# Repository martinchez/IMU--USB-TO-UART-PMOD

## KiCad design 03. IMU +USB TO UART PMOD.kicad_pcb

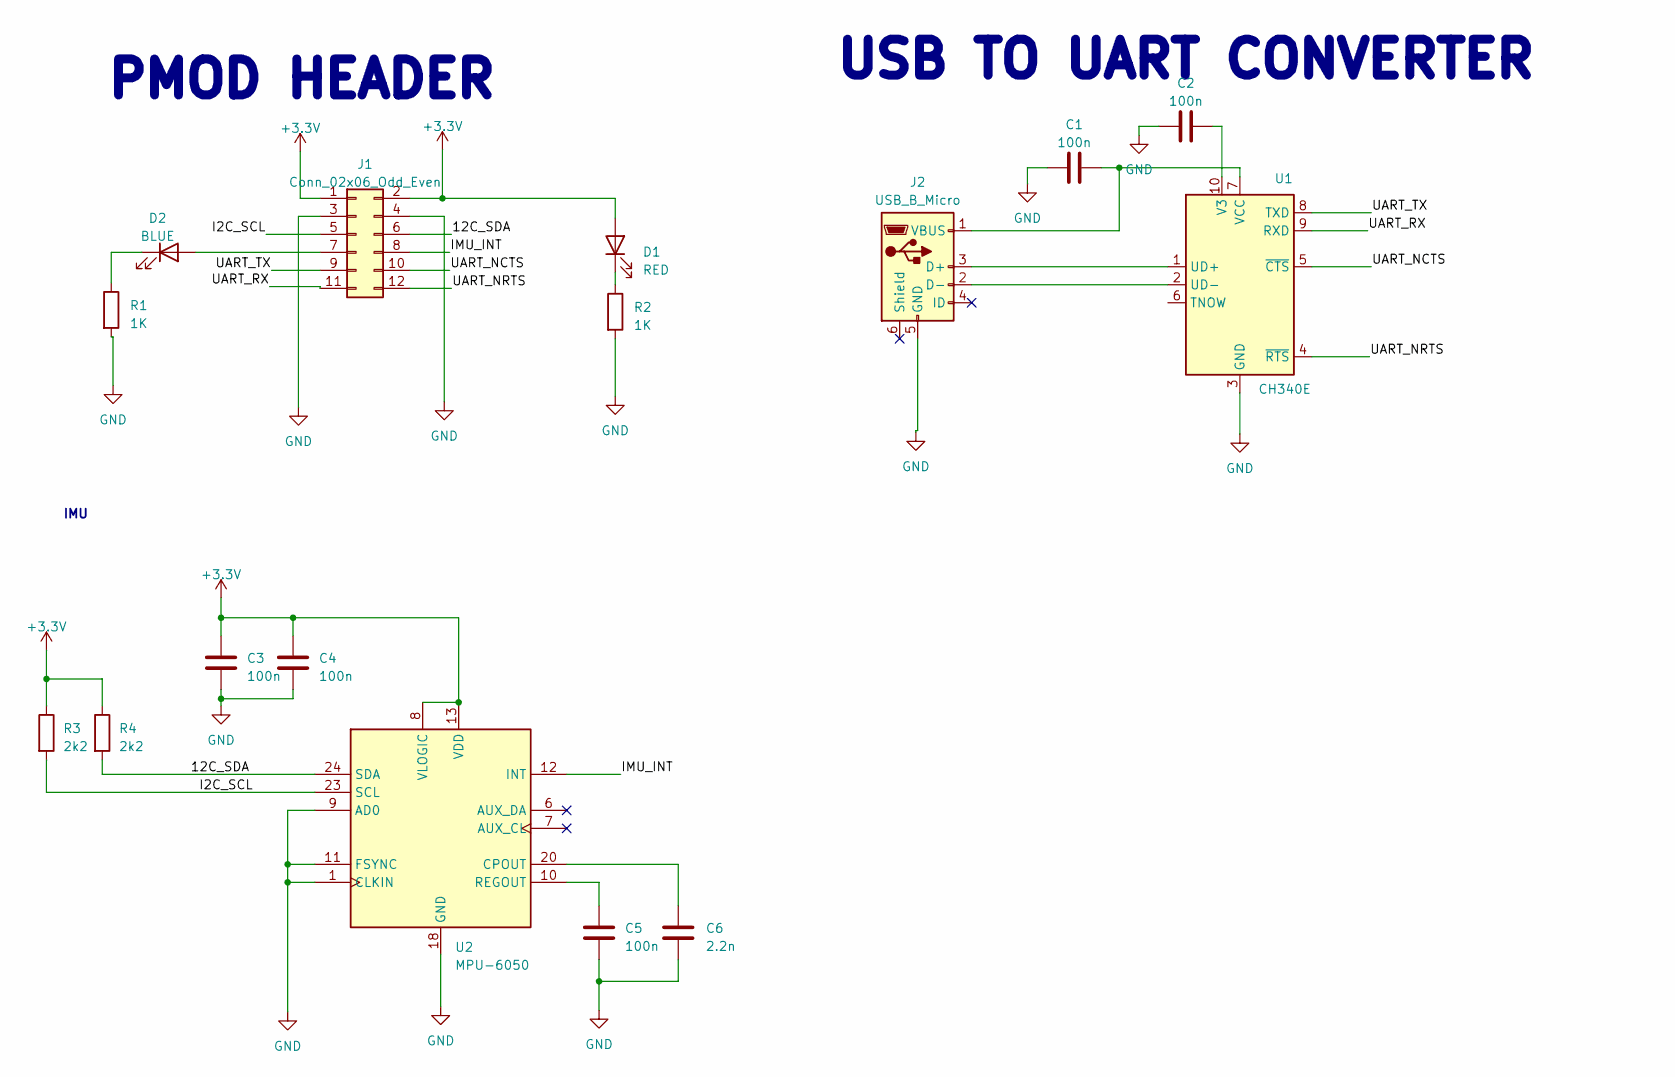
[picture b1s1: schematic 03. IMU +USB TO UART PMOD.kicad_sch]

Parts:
C1, C2, C3, C4, C5: 100n; C_0603_1608Metric
C6: 2.2n; C_0603_1608Metric
D1: RED; LED_0603_1608Metric
D2: BLUE; LED_0603_1608Metric
J1: Conn_02x06_Odd_Even; PinSocket_2x06_P2.54mm_Vertical
J2: USB_B_Micro; USB_Micro-B_Molex-105017-0001
R1, R2: 1K; R_0603_1608Metric
R3, R4: 2k2; R_0612_1632Metric
U1: CH340E; MSOP-10_3x3mm_P0.5mm
U2: MPU-6050; InvenSense_QFN-24_4x4mm_P0.5mm

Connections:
+3.3V: C3.2, C4.2, D1.2 (A), J1.1, J1.2, R3.1, R4.1, U2.8 (VLOGIC), U2.13 (VDD)
/12C_SDA: J1.6, R4.2, U2.24 (SDA)
/I2C_SCL: J1.5, R3.2, U2.23 (SCL)
/IMU_INT: J1.8, U2.12 (INT)
/UART_NCTS: J1.10, U1.5 (~CTS)
/UART_NRTS: J1.12, U1.4 (~RTS)
/UART_RX: J1.11, U1.9 (RXD)
/UART_TX: J1.9, U1.8 (TXD)
GND: C1.1, C2.1, C3.1, C4.1, C5.1, C6.1, J1.3, J1.4, J2.5 (GND), R1.2, R2.2, U1.3 (GND), U2.1 (CLKIN), U2.9 (AD0), U2.11 (FSYNC), U2.18 (GND)
unnamed: D1.1 (K), R2.1
unnamed: D2.2 (A), J1.7
unnamed: D2.1 (K), R1.1
unnamed: J2.3 (D+), U1.1 (UD+)
unnamed: J2.2 (D-), U1.2 (UD-)
unnamed: C1.2, J2.1 (VBUS), U1.7 (VCC)
unnamed: C2.2, U1.10 (V3)
unnamed: C6.2, U2.20 (CPOUT)
unnamed: C5.2, U2.10 (REGOUT)

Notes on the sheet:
PMOD HEADER
IMU
USB TO UART CONVERTER

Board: 2 copper layers, 16 parts (0 on the bottom side), 18 nets, no tracks yet.
